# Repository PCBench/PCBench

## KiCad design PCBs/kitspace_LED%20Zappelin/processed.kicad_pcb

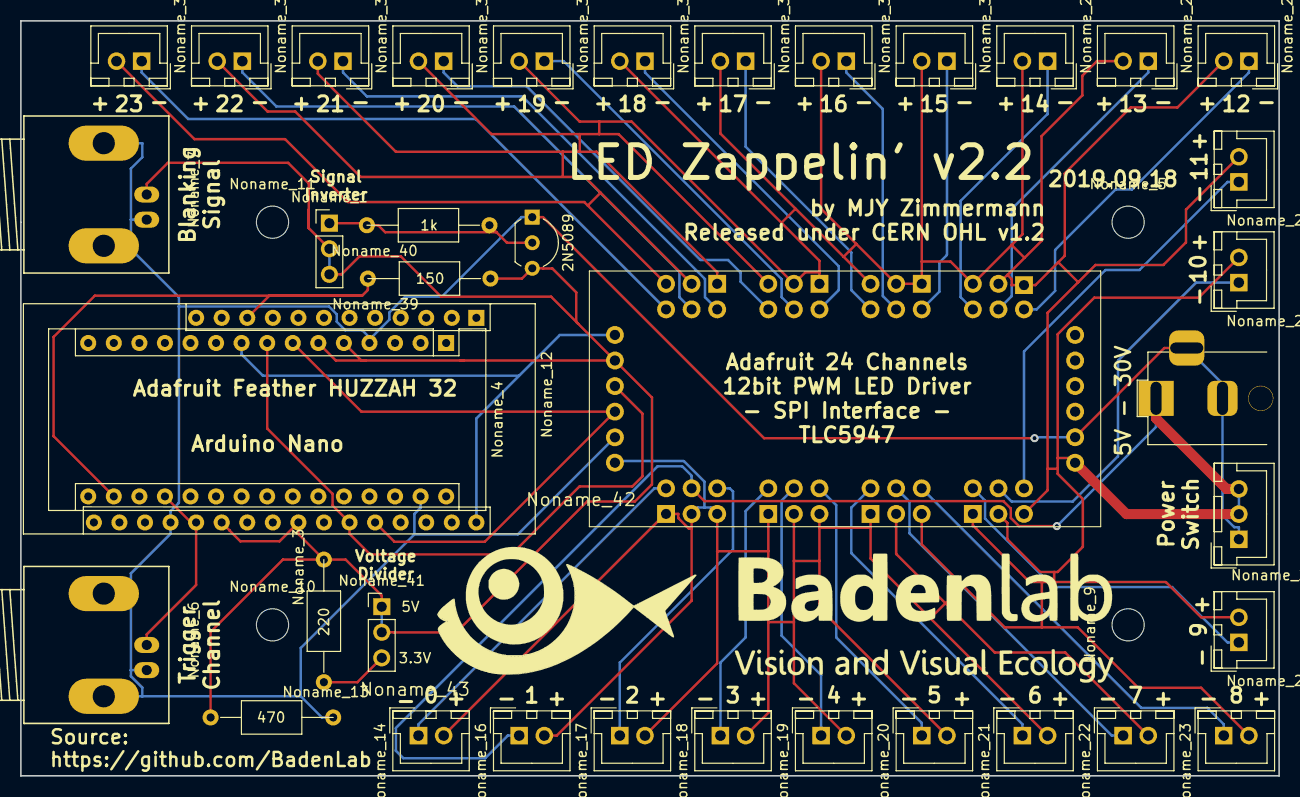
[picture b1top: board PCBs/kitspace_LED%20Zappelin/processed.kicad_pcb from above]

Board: 2 copper layers, 125.0 x 75.0 mm, 45 parts (0 on the bottom side), 34 nets.

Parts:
2N5089: TO-92L_Inline_Wide
J2: 5V - 30V; BarrelJack_Horizontal_maxime
Noname_1, Noname_41: PinHeader_1x03_P2.54mm_Vertical
Noname_2: JST_XH_B03B-XH-A_03x2.50mm_Straight
Noname_3: 220; R_Axial_DIN0309_L9.0mm_D3.2mm_P15.24mm_Horizontal
Noname_4: Arduino Nano; Arduino_Nano
Noname_5, Noname_9, Noname_10, Noname_11: MountingHole_3.2mm_M3_DIN965
Noname_6, Noname_7: BNC_Socket_TYCO-AMP_LargePads
Noname_8: Maxi_TLC5947
Noname_12: Adafruit Huzzah 32
Noname_13: 470; R_Axial_DIN0309_L9.0mm_D3.2mm_P15.24mm_Horizontal
Noname_14, Noname_16, Noname_17, Noname_18, Noname_19, Noname_20, Noname_21, Noname_22, Noname_23, Noname_24, Noname_25, Noname_26, Noname_27, Noname_28, Noname_29, Noname_30, Noname_31, Noname_32, Noname_33, Noname_34, Noname_35, Noname_36, Noname_37, Noname_38: JST_XH_B02B-XH-A_02x2.50mm_Straight
Noname_15: new_logo 1000
Noname_39: 150; R_Axial_DIN0309_L9.0mm_D3.2mm_P15.24mm_Horizontal
Noname_40: 1k; R_Axial_DIN0309_L9.0mm_D3.2mm_P15.24mm_Horizontal
Noname_42, Noname_43: (no value)

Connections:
GNDREF: 2N5089.1, J2.2, J2.3, Noname_2.1, Noname_4.GND, Noname_6.2, Noname_7.2, Noname_8.1, Noname_12.18, Noname_13.2
unnamed: Noname_4.3V3, Noname_12.USB, Noname_39.2
unnamed: Noname_4.A0, Noname_6.1, Noname_12.A0/26
unnamed: 2N5089.3, Noname_1.2, Noname_1.3, Noname_3.2, Noname_4.D2, Noname_4.D3, Noname_7.1, Noname_8.2, Noname_12.A1/25, Noname_12.A4/36, Noname_13.1, Noname_39.1, Noname_41.1, Noname_41.2
unnamed: Noname_4.D5, Noname_8.3, Noname_12.SCK/5
unnamed: Noname_4.D4, Noname_8.4, Noname_12.MOSI/18
unnamed: Noname_4.D6, Noname_8.30, Noname_12.21
unnamed: Noname_3.1, Noname_41.3
unnamed: Noname_8.5, Noname_14.1
unnamed: J2.1, Noname_8.6, Noname_16.1
unnamed: Noname_8.7, Noname_17.1
unnamed: Noname_8.8, Noname_18.1
unnamed: Noname_8.9, Noname_19.1
unnamed: Noname_8.10, Noname_20.1
unnamed: Noname_8.11, Noname_21.1
unnamed: Noname_8.12, Noname_22.1
unnamed: Noname_8.13, Noname_23.1
unnamed: Noname_8.14, Noname_24.1
unnamed: Noname_8.15, Noname_25.1
unnamed: Noname_8.16, Noname_26.1
unnamed: Noname_8.17, Noname_27.1
unnamed: Noname_8.18, Noname_28.1
unnamed: Noname_8.19, Noname_29.1
unnamed: Noname_8.20, Noname_30.1
unnamed: Noname_8.21, Noname_31.1
unnamed: Noname_8.22, Noname_32.1
unnamed: Noname_8.23, Noname_33.1
unnamed: Noname_8.24, Noname_34.1
unnamed: Noname_8.25, Noname_35.1
unnamed: Noname_8.26, Noname_36.1
unnamed: Noname_8.27, Noname_37.1
unnamed: Noname_8.28, Noname_38.1
unnamed: Noname_2.2, Noname_2.3, Noname_8.32, Noname_14.2, Noname_16.2, Noname_17.2, Noname_18.2, Noname_19.2, Noname_20.2, Noname_21.2, Noname_22.2, Noname_23.2, Noname_24.2, Noname_25.2, Noname_26.2, Noname_27.2, Noname_28.2, Noname_29.2, Noname_30.2, Noname_31.2, Noname_32.2, Noname_33.2, Noname_34.2, Noname_35.2, Noname_36.2, Noname_37.2, Noname_38.2
unnamed: 2N5089.2, Noname_1.1, Noname_40.1, Noname_40.2

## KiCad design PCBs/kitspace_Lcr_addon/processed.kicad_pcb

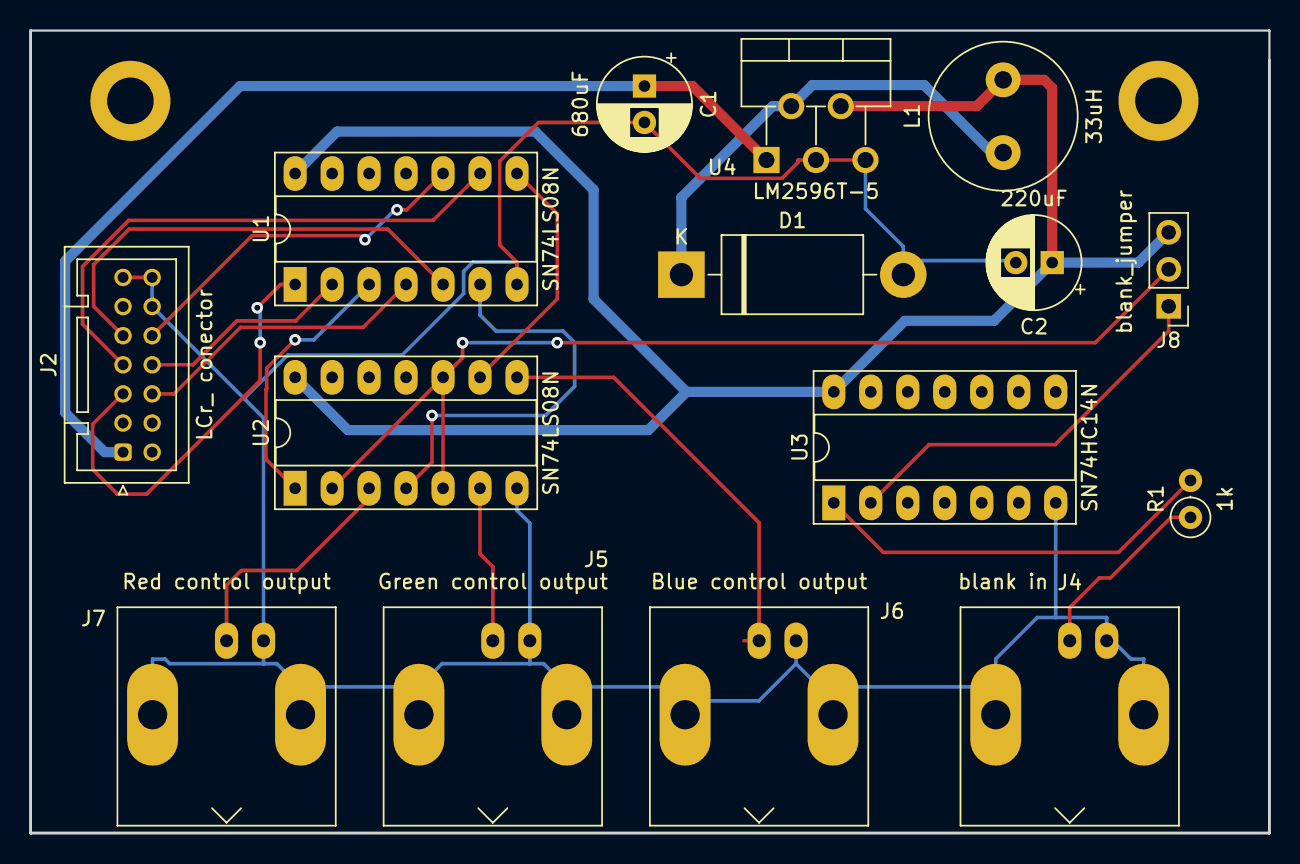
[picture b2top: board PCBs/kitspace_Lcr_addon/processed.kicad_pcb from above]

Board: 2 copper layers, 85.1 x 55.1 mm, 15 parts (0 on the bottom side), 20 nets.

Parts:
C1: 680uF; CP_Radial_D6.3mm_P2.50mm
C2: 220uF; CP_Radial_D6.3mm_P2.50mm
D1: D_Schottky; D_DO-201AD_P15.24mm_Horizontal
J2: LCr_ conector; JST_PUD_B14B-PUDSS_2x07_P2.00mm_Vertical
J4: blank in; BNC_Amphenol_B6252HB-NPP3G-50_Horizontal
J5: Green control output; BNC_Amphenol_B6252HB-NPP3G-50_Horizontal
J6: Blue control output; BNC_Amphenol_B6252HB-NPP3G-50_Horizontal
J7: Red control output; BNC_Amphenol_B6252HB-NPP3G-50_Horizontal
J8: blank_jumper; PinHeader_1x03_P2.54mm_Vertical
L1: 33uH; L_Radial_D10.0mm_P5.00mm_Neosid_SD12_style3
R1: 1k; R_Axial_DIN0207_L6.3mm_D2.5mm_P2.54mm_Vertical
U1, U2: SN74LS08N; DIP-14_W7.62mm_Socket_LongPads
U3: SN74HC14N; DIP-14_W7.62mm_Socket_LongPads
U4: LM2596T-5; TO-220-5_P3.4x3.7mm_StaggerOdd_Lead3.8mm_Vertical

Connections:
+5V: C2.1, J8.3, L1.2, U1.14, U2.14, U3.14, U4.4
+12V: C1.1, J2.1, U4.1
GND: C1.2, C2.2, D1.2, J2.12, J2.13, J2.14, J4.2, J5.2, J6.2, J7.2, U1.7, U2.7, U3.7, U4.3, U4.5
unnamed: D1.1, L1.1, U4.2
unnamed: J4.1, R1.1
unnamed: J5.1, U2.6
unnamed: J6.1, U2.8
unnamed: J7.1, U2.3
unnamed: R1.2, U3.1
unnamed: U1.3, U2.1
unnamed: U1.6, U2.4
unnamed: U1.8, U2.9
blue_sig1: J2.7, U1.9
blue_sig2: J2.10, U1.10
green_sig1: J2.6, U1.4
green_sig2: J2.9, U1.5
inv_blank-or-5V-input: J8.2, U2.2, U2.5, U2.10
inverted_blank: J8.1, U3.2
red_sig1: J2.5, U1.1
red_sig2: J2.8, U1.2

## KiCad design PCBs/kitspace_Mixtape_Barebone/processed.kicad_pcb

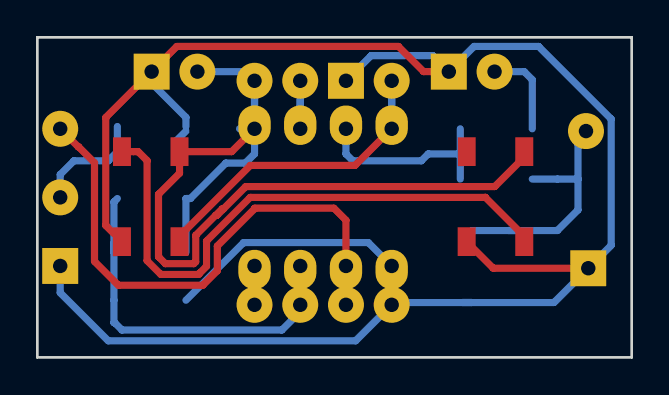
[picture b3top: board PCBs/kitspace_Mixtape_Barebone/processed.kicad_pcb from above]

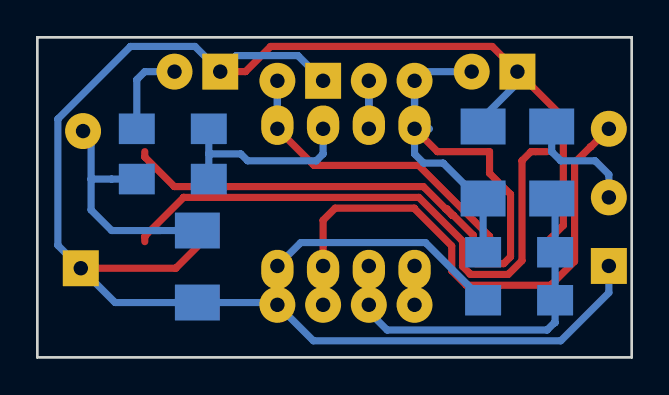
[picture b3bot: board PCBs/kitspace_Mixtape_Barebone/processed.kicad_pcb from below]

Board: 2 copper layers, 33.0 x 17.8 mm, 27 parts (7 on the bottom side), 12 nets.

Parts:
C1, C2, C3: 100nF; C_1210_MixtapeStyle
IC1: ATTINY85-20PU; Attiny_DIP-8_W7.62mm
J1: PB5; Loch_mixtape_seltsam
J2: PB3; Loch_mixtape_seltsam
J3: PB4; Loch_mixtape_seltsam
J3#2: PB4; Loch_mixtape
J4, J4#2: GND; Loch_mixtape_seltsam
J4#3, J4#4, J4#5, J4#6: GND; GND_Loch_mixtape
J5: PB0; Loch_mixtape_seltsam
J7: PB2; Loch_mixtape_seltsam
J8: VCC; Loch_mixtape
J8#2: VCC; Loch_mixtape_seltsam
J9: Prog; Loch_mixtape
J10: S-Out; Loch_mixtape
J11: LED; Loch_mixtape
NEO1, NEO2: SK6813b; Mixtape_NEO_WS2812B
R1, R2: 22K; R_1206_Mixtape
R6: 1K; R_1206_Mixtape
R7: 330; R_1206_Mixtape

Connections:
CV_In: IC1.3, J3.1, J3#2.1
GND: C2.1, C3.1, IC1.4, J4.1, J4#2.1, J4#3.1, J4#4.1, J4#5.1, J4#6.1, NEO1.3, NEO2.3, R2.2
NEO: IC1.5, J5.1, NEO1.4
unnamed: C1.2, J9.1
unnamed: C3.2, J10.1, R7.1
unnamed: J11.1, R6.2
unnamed: IC1.1, J1.1
unnamed: IC1.6, R6.1, R7.2
unnamed: IC1.7, J7.1
unnamed: NEO1.2, NEO2.4
Prog: C1.1, IC1.2, J2.1, R1.2, R2.1
VCC: C2.2, IC1.8, J8.1, J8#2.1, NEO1.1, NEO2.1, R1.1

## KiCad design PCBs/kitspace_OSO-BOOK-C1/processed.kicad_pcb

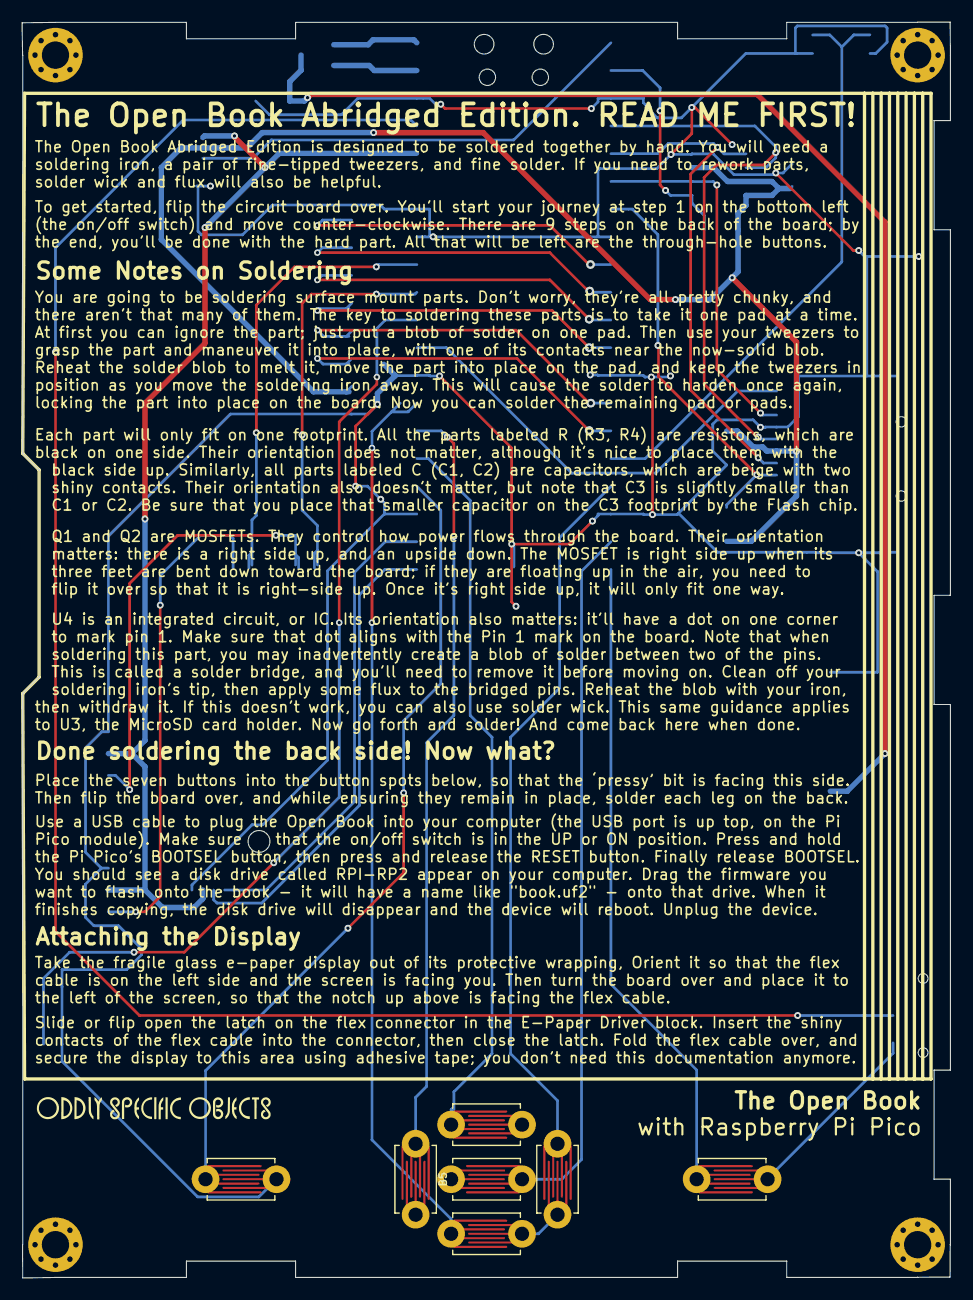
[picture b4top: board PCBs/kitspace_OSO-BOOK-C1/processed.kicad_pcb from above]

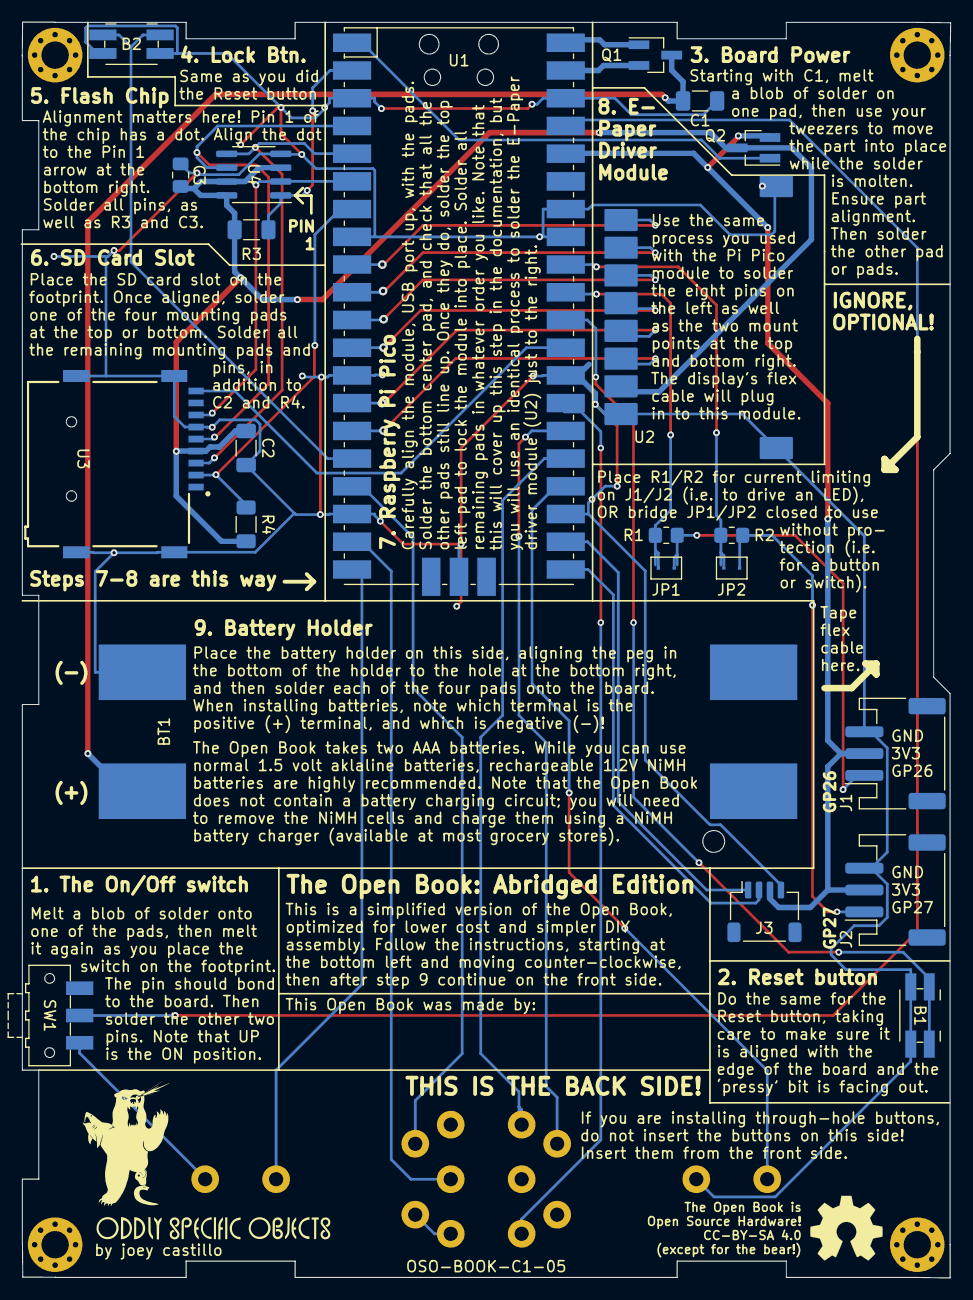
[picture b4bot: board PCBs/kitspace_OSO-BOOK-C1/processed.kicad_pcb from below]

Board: 2 copper layers, 85.1 x 115.1 mm, 36 parts (25 on the bottom side), 35 nets.

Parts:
B1, B2: SW_Push; Panasonic_EVQPUJ_EVQPUA
B3, B4, B5, B6, B7, B8, B9: SW_Push; TACT_PANA-EVQ-BUTTONPAD
BT1: Battery; AAA_SMT
C1, C2: 10µF; C_1206_3216Metric_Pad1.33x1.80mm_HandSolder
C3: 1µF; C_0805_2012Metric_Pad1.18x1.45mm_HandSolder
G1, G2: LOGO; oso-logotype-2mm
G3: LOGO; oso-bear-8mm-wide
J1, J2: JST-PH3; JST_PH_S3B-PH-SM4-TB_1x03-1MP_P2.00mm_Horizontal
J3: JST-PH4; JST_SH_SM04B-SRSS-TB_1x04-1MP_P1.00mm_Horizontal
JP1, JP2: Jumper_2_Open; SolderJumper-2_P1.3mm_Open_TrianglePad1.0x1.5mm
Q1, Q2: Q_PMOS_GSD; SOT-23_Handsoldering
R1, R2: 1k; R_0805_2012Metric_Pad1.20x1.40mm_HandSolder
R3, R4: 10K; R_1206_3216Metric_Pad1.30x1.75mm_HandSolder
REF1, REF2, REF4: MountingHole_2.5mm_Pad_Via
REF5: OSHW-Symbol_6.7x6mm_SilkScreen
SW1: SW_SPDT; SW_SPDT_CK-JS102011SAQN
U1: Pico; RPi_Pico_SMD
U2: OSO-BOOK-C2-01
U3: MEM2075; GCT_MEM2075-00-140-01-A
U4: GD25Q16C; SOIC-8_3.9x4.9mm_P1.27mm

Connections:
+3.3VP: C2.2, C3.1, Q2.3, R3.2, R4.2, U2.7, U3.P4, U4.3, U4.7, U4.8
+3V3: J1.2, J2.2, J3.3, Q2.2, U1.36
+BATT: BT1.1, C1.1, Q1.3
/BABEL_CS: R3.1, U1.2, U4.1
/BTN_DOWN: B8.1, U1.27
/BTN_LEFT: B5.1, U1.26
/BTN_LOCK: B2.1, U1.16
/BTN_NEXT: B4.1, U1.20
/BTN_PREV: B3.1, U1.24
/BTN_RIGHT: B9.1, U1.17
/BTN_SEL: B7.1, U1.19
/BTN_UP: B6.1, U1.25
/DISPLAY_BUSY: U1.9, U2.1
/DISPLAY_CS: U1.12, U2.4
/DISPLAY_DC: U1.11, U2.3
/DISPLAY_MOSI: U1.15, U2.6
/DISPLAY_RESET: U1.10, U2.2
/DISPLAY_SCK: U1.14, U2.5
/EN: SW1.2, U1.37
/GP26: JP1.2, R1.1, U1.31
/GP27: JP2.2, R2.1, U1.32
/MISO: U1.6, U3.P7, U4.2
/MOSI: U1.5, U3.P3, U4.5
/RESET: B1.1, U1.30
/RX/SCL: J3.1, U1.22
/SCK: U1.4, U3.P5, U4.6
/SD_CD: U1.29, U3.P9
/SD_CS: R4.1, U1.7, U3.P2
/TX/SDA: J3.2, U1.21
/_GP26: J1.1, JP1.1, R1.2
/_GP27: J2.1, JP2.1, R2.2
/~EN2: Q2.1, U1.1
GND: B1.2, B2.2, B3.2, B4.2, B5.2, B6.2, B7.2, B8.2, B9.2, BT1.2, C1.2, C2.1, C3.2, J1.3, J2.3, J3.4, SW1.3, U1.3, U1.8, U1.13, U1.18, U1.23, U1.28, U1.33, U1.34, U1.38, U1.42, U2.8, U2.9, U2.10, U3.P6, U3.SH1, U3.SH2, U3.SH3, U3.SH4, U4.4
VBUS: Q1.1, U1.40
VCC: Q1.2, U1.39

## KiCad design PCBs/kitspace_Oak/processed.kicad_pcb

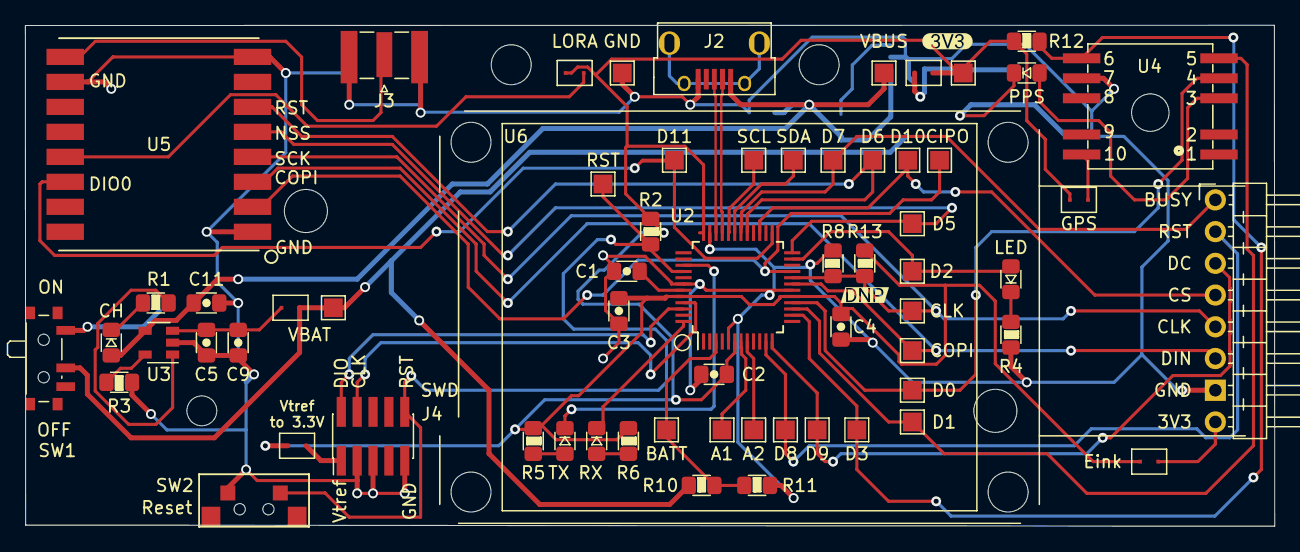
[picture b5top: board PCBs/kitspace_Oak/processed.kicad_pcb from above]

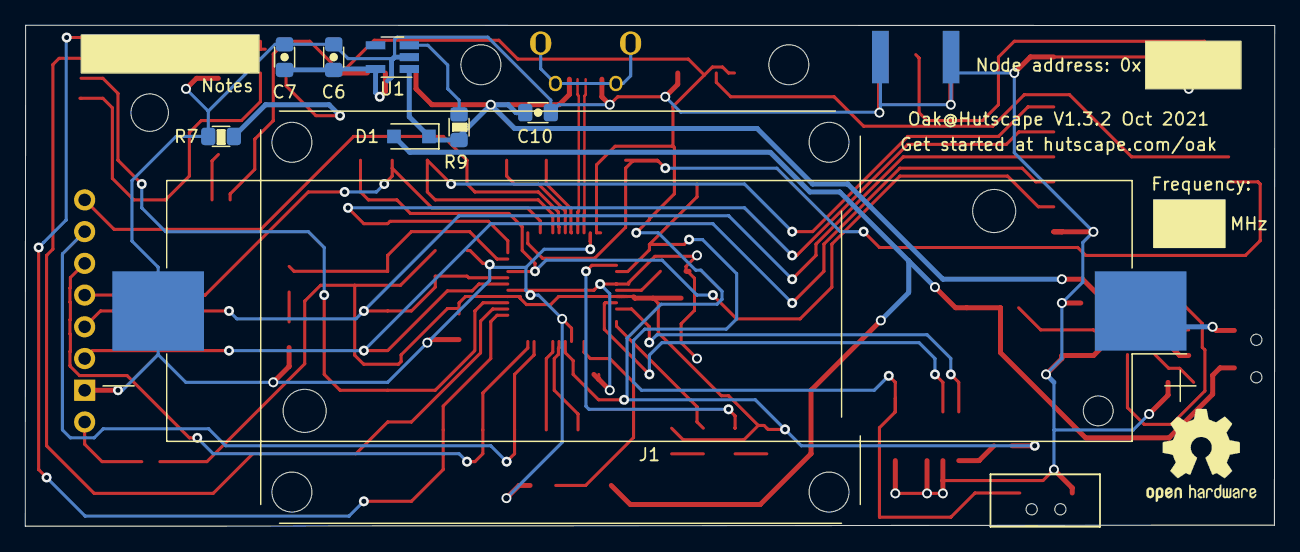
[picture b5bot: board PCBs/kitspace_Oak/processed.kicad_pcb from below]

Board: 2 copper layers, 100.0 x 40.1 mm, 76 parts (9 on the bottom side), 48 nets.

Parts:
C1, C7, C9: 1uF; C_0805_2012Metric_Pad1.15x1.40mm_HandSolder
C2, C3, C4: 100nF; C_0805_2012Metric_Pad1.15x1.40mm_HandSolder
C5, C6, C10, C11: 10uF; C_0805_2012Metric_Pad1.15x1.40mm_HandSolder
D1: D_Schottky; D_SOD-123F
D2: ORANGE; LED_0805_2012Metric_Pad1.15x1.40mm_HandSolder
D3: RED; LED_0805_2012Metric_Pad1.15x1.40mm_HandSolder
D4, D5, D6: YELLOW; LED_0805_2012Metric_Pad1.15x1.40mm_HandSolder
J1: 18650 Battery holder; BatteryHolder_Keystone_1042_1x18650
J2: USB_B_Micro; USB_Micro-B_Horizontal-U254-051T-4BH23-S2B
J3: Conn_Coaxial; SMA_Samtec_SMA-J-P-X-ST-EM1_EdgeMount
J4: Conn_ARM_JTAG_SWD_10; PinHeader_2x05_P1.27mm_Vertical_SMD
JP1, JP2, JP3, JP4, JP5, JP6: SolderJumper_2_Open; SolderJumper-2_P1.3mm_Open_TrianglePad1.0x1.5mm
R1, R4, R5, R6, R7, R8: 1k; R_0805_2012Metric_Pad1.15x1.40mm_HandSolder
R2, R3, R12: 10k; R_0805_2012Metric_Pad1.15x1.40mm_HandSolder
R9, R10, R11: 100k; R_0805_2012Metric_Pad1.15x1.40mm_HandSolder
R13: DNP; R_0805_2012Metric_Pad1.15x1.40mm_HandSolder
REF1, REF2: MountingHole_3.2mm_M3
REF3: OSHW-Logo2_9.8x8mm_SilkScreen
SW1: SW_SPDT; SW_SPDT_PCM12
SW2: SW_Push; Tactile_pushbutton
TP1, TP2, TP3, TP4, TP5, TP6, TP7, TP8, TP9, TP10, TP11, TP12, TP13, TP14, TP15, TP16, TP17, TP18, TP19, TP20, TP21, TP22, TP23, TP24: TestPoint_Probe; TestPoint_Pad_1.5x1.5mm
U1: AP2112; SOT-23-5_HandSoldering
U2: ATSAMD21; TQFP-48_7x7mm_P0.5mm
U3: MCP7383; SOT-23-5
U4: PA1010D; CDTop_MT3333_PA1010D
U5: RFM95; HopeRF_RFM9X-SMD
U6: Waveshare_1in54_epaper; Waveshare_1.54_E-Ink
e: G***; label
svg2mod: G***; label

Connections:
+3V3: C2.1, C3.1, C4.1, JP1.1, JP3.1, JP4.1, JP5.1, JP6.1, R2.1, R5.1, R6.1, R12.1, R13.1, TP4.1, U2.6, U2.17, U2.36, U2.44
/A1: TP7.1, U2.7
/A2: TP6.1, U2.8
/BATT: R10.2, R11.1, TP8.1, U2.3
/CIPO: TP21.1, U2.21, U5.2
/CLK: R8.1, R13.2, TP16.1, U2.20, U5.4, U6.5
/COPI: TP5.1, U2.19, U5.3, U6.6
/EINK_BUSY: TP19.1, U2.30, U6.1
/EINK_CS: TP22.1, U2.27, U6.4
/EINK_DC: TP10.1, U2.12, U6.3
/EINK_RST: TP9.1, U2.11, U6.2
/GPS_RST: R12.2, TP11.1, U2.14, U4.6
/GPS_RX: TP12.1, U2.15, U4.5
/GPS_TX: TP13.1, U2.16, U4.4
/LED: D6.2, TP14.1, U2.23
/LORA_CS: TP15.1, U2.24, U5.5
/LORA_DATA: TP24.1, U2.25, U5.14
/LORA_RST: TP20.1, U2.29, U5.6
/RST: J4.10, R2.2, SW2.1, TP23.1, U2.40
/RX_LED: D5.1, U2.48
/SCL: TP18.1, U2.32
/SDA: TP17.1, U2.31
/SWCLK: J4.4, U2.45
/SWDIO: J4.2, U2.46
/TX_LED: D4.1, U2.39
/USB_D+: J2.3, U2.34
/USB_D-: J2.2, U2.33
/VBAT: D1.2, JP2.1, R10.1, SW1.2, TP1.1
/VBUS: C10.1, C11.2, D1.1, D2.2, J2.1, R9.2, TP2.1, U1.1, U3.4
GND: C1.1, C2.2, C3.2, C4.2, C5.1, C6.2, C7.2, C9.1, C10.2, C11.1, J1.2, J2.5, J3.2, J4.3, J4.5, J4.9, R3.1, R4.2, R7.2, R8.2, R11.2, SW2.2, TP3.1, U1.2, U2.5, U2.18, U2.35, U2.42, U3.2, U4.7, U5.1, U5.8, U5.10, U6.7
unnamed: C1.2, U2.43
unnamed: C5.2, C9.2, JP2.2, U3.3
unnamed: C6.1, C7.1, JP1.2, U1.5
unnamed: D2.1, R1.1
unnamed: D3.1, R7.1
unnamed: D3.2, U4.3
unnamed: D4.2, R5.2
unnamed: D5.2, R6.2
unnamed: D6.1, R4.1
unnamed: J1.1, SW1.1
unnamed: J3.1, U5.9
unnamed: J4.1, JP6.2
unnamed: JP3.2, U4.10
unnamed: JP4.2, U5.13
unnamed: JP5.2, U6.8
unnamed: R1.2, U3.1
unnamed: R3.2, U3.5
unnamed: R9.1, U1.3

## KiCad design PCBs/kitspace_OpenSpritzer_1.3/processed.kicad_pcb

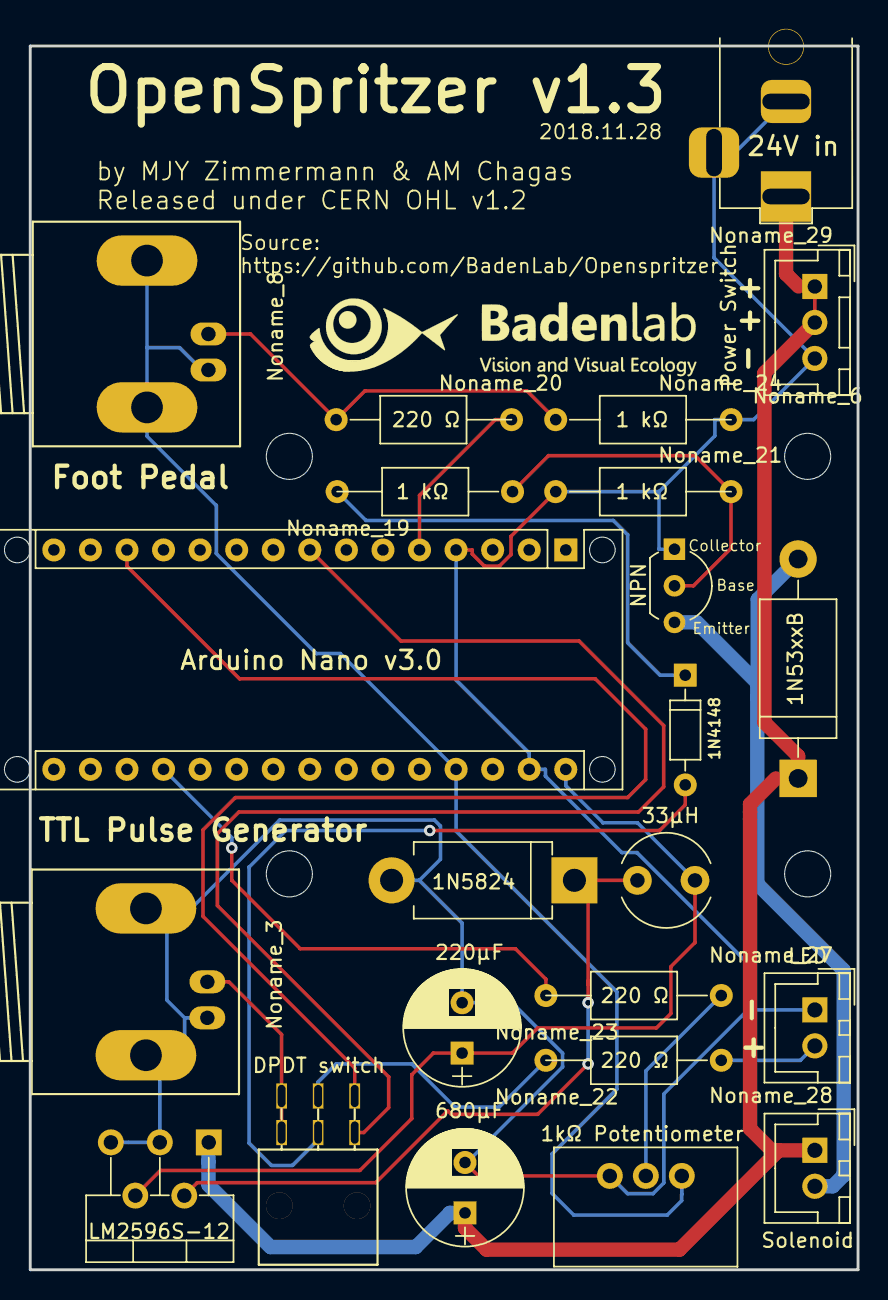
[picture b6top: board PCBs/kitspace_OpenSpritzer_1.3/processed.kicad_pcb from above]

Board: 2 copper layers, 57.5 x 85.0 mm, 28 parts (0 on the bottom side), 18 nets.

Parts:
NPN: TO-92L_Inline_Wide
Noname_2: new_logo 2500
Noname_3: TTL Pulse Generator; BNC_Socket_TYCO-AMP_LargePads
Noname_4, Noname_6, Noname_9, Noname_10: MountingHole_3.2mm_M3
Noname_5: LM2596S-12; TO-220-5_Vertical_StaggeredType1
Noname_7: 1N4148; D_DO-35_SOD27_P7.62mm_Horizontal
Noname_8: Foot Pedal; BNC_Socket_TYCO-AMP_LargePads
Noname_11: 220μF; CP_Radial_D8.0mm_P3.50mm
Noname_12: 680μF; CP_Radial_D8.0mm_P3.50mm
Noname_13: DPDT switch; maxi_DPDT_Angled
Noname_14: 1N5824; D_DO-201AD_P12.70mm_Horizontal
Noname_16: 24V in; BarrelJack_Horizontal_maxime
Noname_17: Arduino Nano v3.0; Arduino_Nano_WithMountingHoles
Noname_18: 33μH; L_Radial_D6.0mm_P4.00mm
Noname_19, Noname_21, Noname_24: 1 kΩ; R_Axial_DIN0309_L9.0mm_D3.2mm_P15.24mm_Horizontal
Noname_20, Noname_22, Noname_23: 220 Ω; R_Axial_DIN0309_L9.0mm_D3.2mm_P15.24mm_Horizontal
Noname_25: 1N53xxB; D_DO-201_P15.24mm_Horizontal
Noname_26: 1kΩ Potentiometer; Potentiometer
Noname_27: LED; JST_XH_B02B-XH-A_02x2.50mm_Straight
Noname_28: Solenoid; JST_XH_B02B-XH-A_02x2.50mm_Straight
Noname_29: Power Switch; JST_XH_B03B-XH-A_03x2.50mm_Straight

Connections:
GNDREF: NPN.1, Noname_3.2, Noname_5.3, Noname_5.5, Noname_11.2, Noname_12.2, Noname_14.2, Noname_16.2, Noname_16.3, Noname_17.4, Noname_17.29, Noname_21.1, Noname_24.2, Noname_26.1, Noname_27.1, Noname_29.3
unnamed: Noname_17.5, Noname_20.2
unnamed: Noname_13.6, Noname_17.8
unnamed: Noname_13.3, Noname_17.13
unnamed: Noname_17.19, Noname_23.2
unnamed: Noname_8.2, Noname_17.27, Noname_26.3
unnamed: Noname_5.4, Noname_11.1, Noname_17.30, Noname_18.1
unnamed: Noname_5.1, Noname_12.1, Noname_16.1, Noname_25.1, Noname_28.1, Noname_29.1, Noname_29.2
unnamed: Noname_22.1, Noname_27.2
unnamed: Noname_7.1, Noname_19.2
unnamed: Noname_7.2, Noname_13.5
unnamed: NPN.3, Noname_25.2, Noname_28.2
unnamed: Noname_5.2, Noname_14.1, Noname_18.2
unnamed: Noname_8.1, Noname_20.1, Noname_24.1
unnamed: Noname_3.1, Noname_13.1, Noname_13.4
unnamed: NPN.2, Noname_19.1, Noname_21.2
unnamed: Noname_23.1, Noname_26.2
unnamed: Noname_13.2, Noname_22.2

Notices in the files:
PCBs/kitspace_LED%20Zappelin/processed.kicad_pcb:
Released under CERN OHL v1.2
PCBs/kitspace_OSO-BOOK-C1/processed.kicad_pcb:
CC-BY-SA 4.0
PCBs/kitspace_Oak/processed.kicad_pcb:
License: CC-BY-SA 4.0 or TAPR
